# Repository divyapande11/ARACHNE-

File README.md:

# ARACHNE-
ARACHNE is a 6-legged, 12-servo walking robot built around two focused technical challenges, deliberately scoped down from an earlier multi-part design to ensure depth over breadth: coordinated multi-servo gait generation and real-time obstacle detection with behavioral response. The project uses an ESP32-S3 as the control core, a custom PCB, and a modified mechanical frame of bot having six legs and a main body.

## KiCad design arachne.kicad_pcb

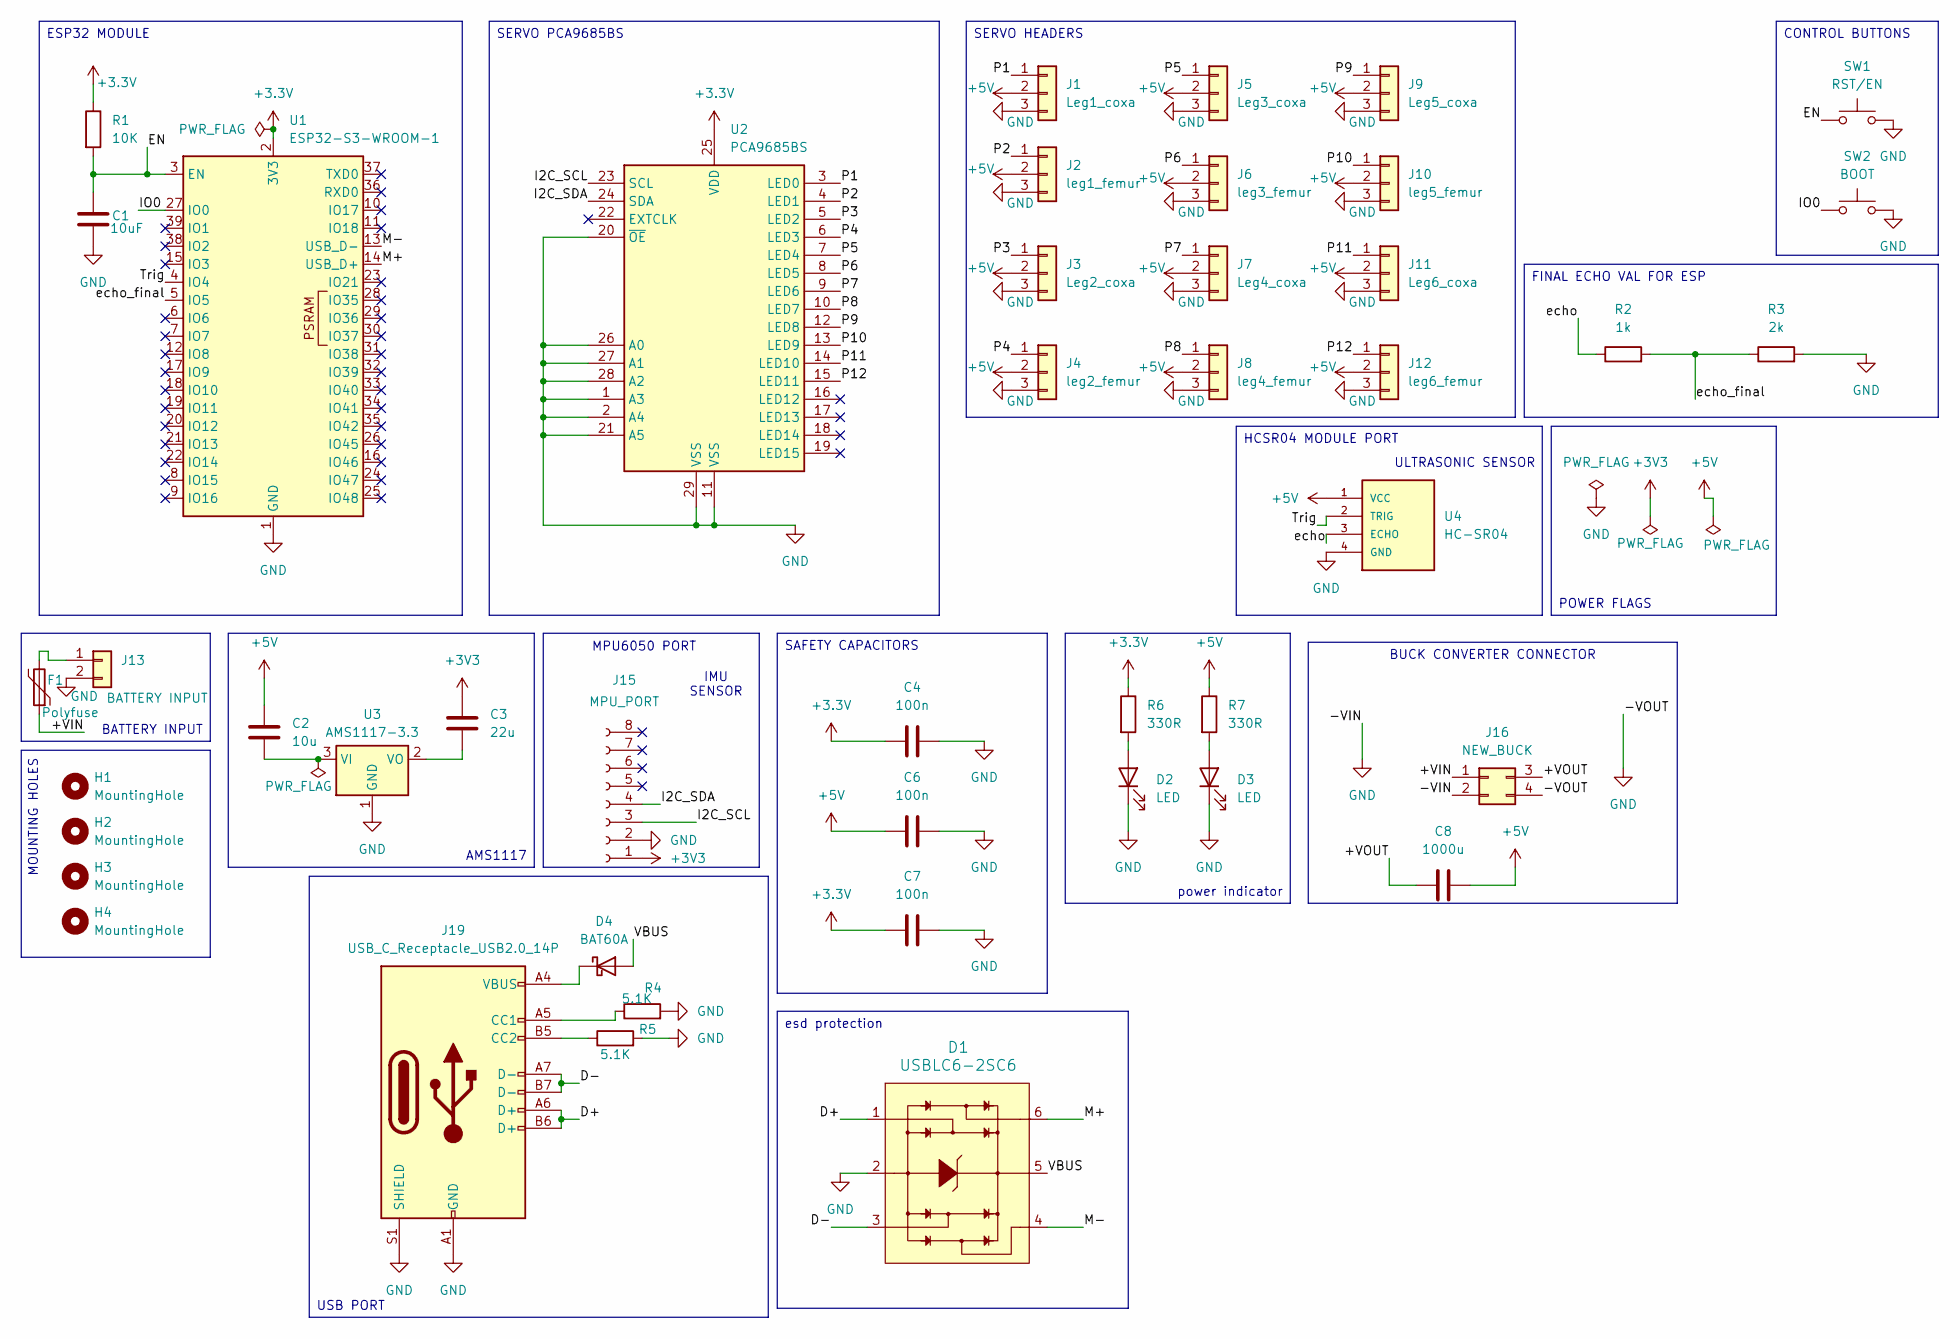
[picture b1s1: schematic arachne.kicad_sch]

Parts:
C1: 10uF; C_0805_2012Metric
C2: 10u; C_0805_2012Metric
C3: 22u; C_1206_3216Metric
C4, C6, C7: 100n; C_0805_2012Metric
C8: 1000u; C_Radial_D10.0mm_H12.5mm_P5.00mm
D1: USBLC6-2SC6; SOT-23-6; MPN USBLC6-2SC6; Digi-Key_PN 497-5235-1-ND
D2, D3: LED; LED_0603_1608Metric
D4: BAT60A; D_SOD-323
F1: Polyfuse; Fuse_1206_3216Metric
H1, H2, H3, H4: MountingHole; MountingHole_3.2mm_M3
J1: Leg1_coxa; PinHeader_1x03_P2.54mm_Vertical
J2: leg1_femur; PinHeader_1x03_P2.54mm_Vertical
J3: Leg2_coxa; PinHeader_1x03_P2.54mm_Vertical
J4: leg2_femur; PinHeader_1x03_P2.54mm_Vertical
J5: Leg3_coxa; PinHeader_1x03_P2.54mm_Vertical
J6: leg3_femur; PinHeader_1x03_P2.54mm_Vertical
J7: Leg4_coxa; PinHeader_1x03_P2.54mm_Vertical
J8: leg4_femur; PinHeader_1x03_P2.54mm_Vertical
J9: Leg5_coxa; PinHeader_1x03_P2.54mm_Vertical
J10: leg5_femur; PinHeader_1x03_P2.54mm_Vertical
J11: Leg6_coxa; PinHeader_1x03_P2.54mm_Vertical
J12: leg6_femur; PinHeader_1x03_P2.54mm_Vertical
J13: BATTERY INPUT; TerminalBlock_Phoenix_MKDS-1,5-2-5.08_1x02_P5.08mm_Horizont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
J15: MPU_PORT; PinHeader_1x08_P2.54mm_Vertical
J16: NEW_BUCK; PinHeader_2x02_P2.54mm_Vertical
J19: USB_C_Receptacle_USB2.0_14P; USB_C_Receptacle_HRO_TYPE-C-31-M-12
R1: 10K; R_0805_2012Metric
R2: 1k; R_0805_2012Metric
R3: 2k; R_0805_2012Metric
R4, R5: 5.1K; R_0805_2012Metric
R6, R7: 330R; R_0805_2012Metric
SW1: RST/EN; SW_PUSH_6mm
SW2: BOOT; SW_PUSH_6mm
U1: ESP32-S3-WROOM-1
U2: PCA9685BS; QFN-28-1EP_6x6mm_P0.65mm_EP4.25x4.25mm
U3: AMS1117-3.3; SOT-223-3_TabPin2
U4: HC-SR04; XCVR_HC-SR04

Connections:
+3.3V: C4.1, C7.1, R1.1, R6.1, U1.2 (3V3), U2.25 (VDD)
+3V3: C3.1, J15.1
+5V: C2.1, C6.1, C8.1, J1.2, J2.2, J3.2, J4.2, J5.2, J6.2, J7.2, J8.2, J9.2, J10.2, J11.2, J12.2, R7.1, U4.1 (VCC)
/+VIN: F1.1, J16.1
/+VOUT: C8.2, J16.3
/D+: D1.1, J19.A6 (D+), J19.B6 (D+)
/D-: D1.3, J19.A7 (D-), J19.B7 (D-)
/EN: C1.1, R1.2, SW1.1, U1.3 (EN)
/I2C_SCL: J15.3, U2.23 (SCL)
/I2C_SDA: J15.4, U2.24 (SDA)
/IO0: SW2.1, U1.27 (IO0)
/M+: D1.6, U1.14 (USB_D+)
/M-: D1.4, U1.13 (USB_D-)
/P1: J1.1, U2.3 (LED0)
/P2: J2.1, U2.4 (LED1)
/P3: J3.1, U2.5 (LED2)
/P4: J4.1, U2.6 (LED3)
/P5: J5.1, U2.7 (LED4)
/P6: J6.1, U2.8 (LED5)
/P7: J7.1, U2.9 (LED6)
/P8: J8.1, U2.10 (LED7)
/P9: J9.1, U2.12 (LED8)
/P10: J10.1, U2.13 (LED9)
/P11: J11.1, U2.14 (LED10)
/P12: J12.1, U2.15 (LED11)
/Trig: U1.4 (IO4), U4.2 (TRIG)
/VBUS: D1.5, D4.2 (A)
/echo: R2.1, U4.3 (ECHO)
/echo_final: R2.2, R3.1, U1.5 (IO5)
GND: C1.2, C4.2, C6.2, C7.2, D1.2, D2.1 (K), D3.1 (K), J1.3, J2.3, J3.3, J4.3, J5.3, J6.3, J7.3, J8.3, J9.3, J10.3, J11.3, J12.3, J13.2, J15.2, J16.2, J16.4, J19.A1 (GND), J19.A12 (GND), J19.B1 (GND), J19.B12 (GND), J19.S1 (SHIELD), R3.2, R4.2, R5.2, SW1.2, SW2.2, U1.1 (GND), U1.40 (GND), U1.41 (GND), U2.1 (A3), U2.2 (A4), U2.11 (VSS), U2.20 (~OE), U2.21 (A5), U2.26 (A0), U2.27 (A1), U2.28 (A2), U2.29 (VSS), U3.1 (GND), U4.4 (GND)
unnamed: D2.2 (A), R6.2
unnamed: D3.2 (A), R7.2
unnamed: D4.1 (K), J19.A4 (VBUS), J19.A9 (VBUS), J19.B4 (VBUS), J19.B9 (VBUS)
unnamed: F1.2, J13.1
unnamed: J19.A5 (CC1), R4.1
unnamed: J19.B5 (CC2), R5.1
unnamed: C2.2, U3.3 (VI)
unnamed: C3.2, U3.2 (VO)

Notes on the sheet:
MPU6050 PORT
IMU SENSOR
ULTRASONIC SENSOR
BATTERY INPUT
USB PORT
MOUNTING HOLES
CONTROL BUTTONS
POWER FLAGS
SERVO PCA9685BS
SERVO HEADERS
BUCK CONVERTER CONNECTOR
HCSR04 MODULE PORT
power indicator
AMS1117
ESP32 MODULE
SAFETY CAPACITORS
FINAL ECHO VAL FOR ESP
esd protection

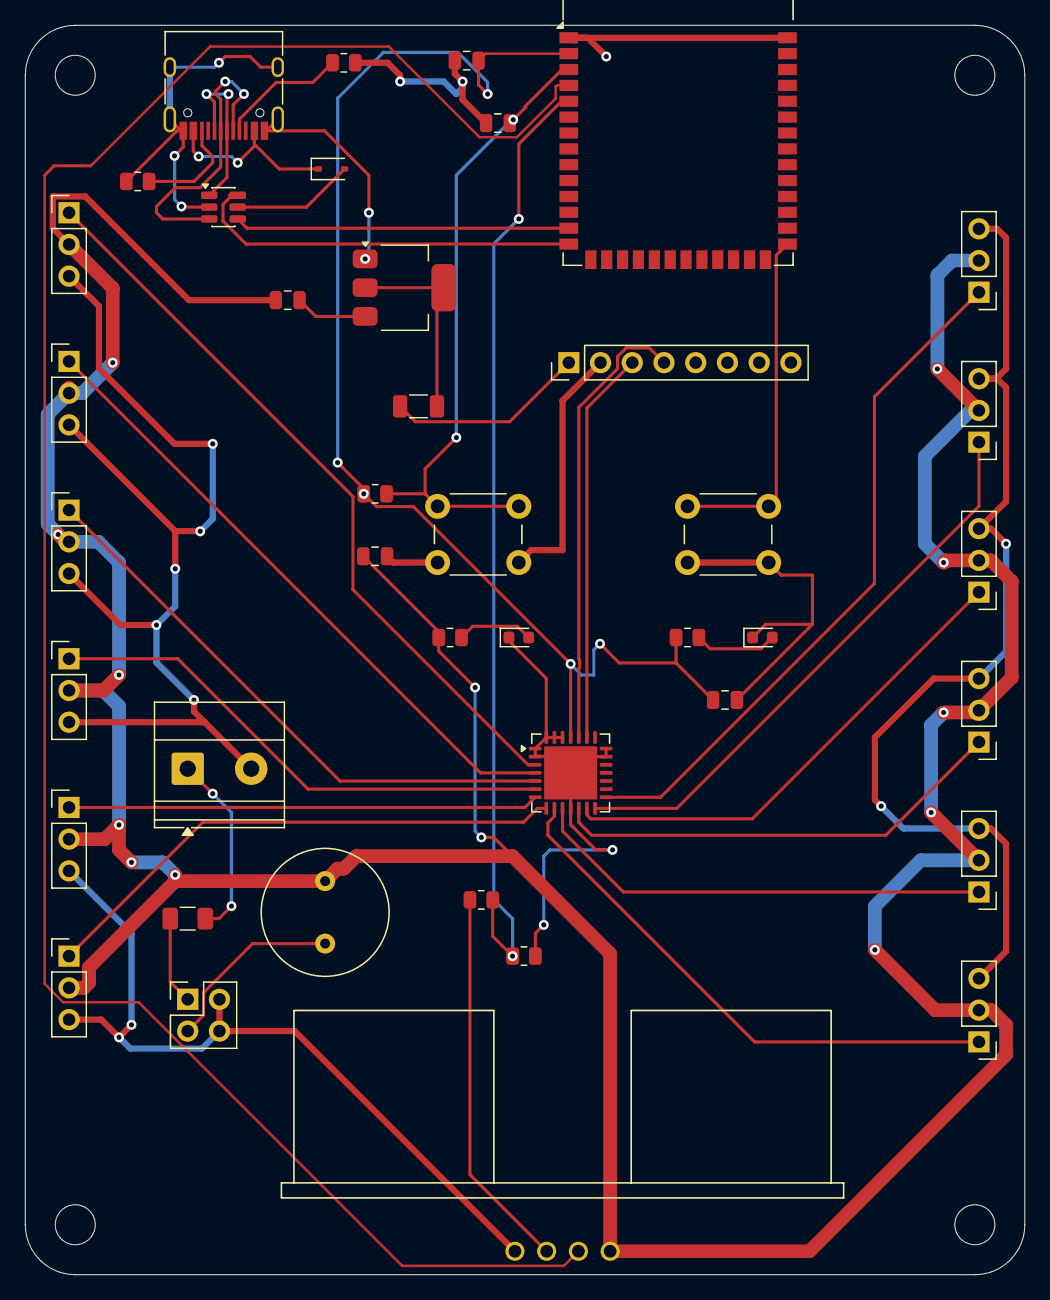
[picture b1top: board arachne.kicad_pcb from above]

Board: 2 copper layers, 80.0 x 100.0 mm, 45 parts (0 on the bottom side), 38 nets.
